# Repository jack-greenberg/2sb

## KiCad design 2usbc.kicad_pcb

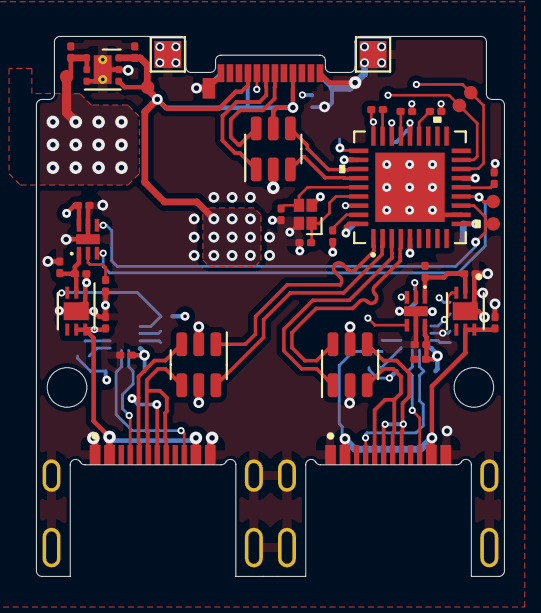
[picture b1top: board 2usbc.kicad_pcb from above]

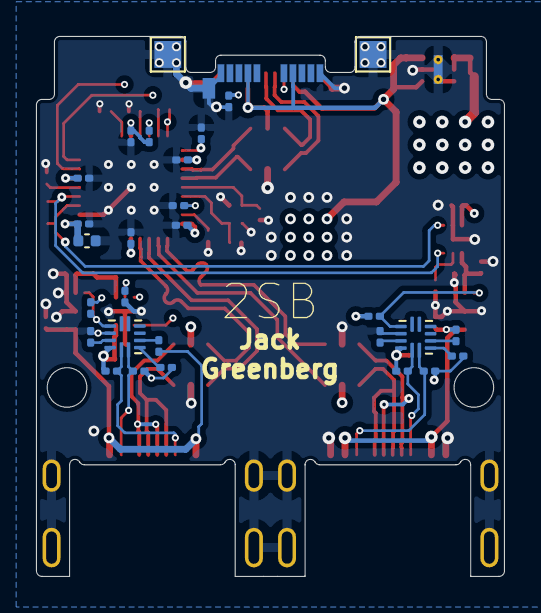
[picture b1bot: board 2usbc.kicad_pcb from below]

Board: 4 copper layers, 26.0 x 30.0 mm, 71 parts (28 on the bottom side), 48 nets.

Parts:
C101, C304, C404: 1uF; C_0201_0603Metric
C102: 2.2uF; C_0201_0603Metric
C201, C203, C205, C206, C207, C208: 10nF; C_0201_0603Metric
C202, C204: 6pF; C_0201_0603Metric
C209, C211, C301, C302, C305, C401, C402, C405: 0.1uF; C_0201_0603Metric
C210: 2uF; C_0402_1005Metric
C303, C403: 10uF; C_0201_0603Metric
H101, H102: MountingHole; MountingHole_2.2mm_M2
J101: USB_C_Plug_USB2.0; USB_C_Plug_Molex_105444
J102, J103: USB_C_Receptacle_USB2.0; USB4520
R101: 5.1K; R_0201_0603Metric
R201, R204, R205, R206, R207, R305, R405: 100K; R_0201_0603Metric
R208: 12K; R_0201_0603Metric
R301, R401: 330R; R_0201_0603Metric
R302, R303, R402, R403: 56K; R_0201_0603Metric
R304, R404: 900K; R_0201_0603Metric
R306, R406: 10K; R_0201_0603Metric
R307, R407: 10k; R_0201_0603Metric
TP101, TP102, TP103, TP104: TestPoint; TestPoint_Pad_1.5x1.5mm
TP105, TP106, TP301, TP302, TP401, TP402: TestPoint; TestPoint_MD
U101: TLV76733DRVx; WSON-6-1EP_2x2mm_P0.65mm_EP1x1.6mm_ThermalVias
U102, U301, U401: USBLC6-2SC6; SOT-23-6
U201: USB2512B; USB2512-AEZG
U302, U402: TMLF-6_MT_MCH; MIC2097-1YMT-TR
U303, U403: TUSB320; Texas_X2QFN-12_1.6x1.6mm_P0.4mm
U304, U404: AP2161W; SON50P181X201X60-7N
Y201: 24MHz; XTAL_ABM12W-24.0000MHZ-6-D1X-T3

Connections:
+3V3: C102.1, C201.1, C203.1, C205.1, C206.1, C207.1, C208.1, C210.1, R201.1, R207.1, TP106.1, U101.1 (OUT), U101.2 (SNS), U201.5 (VDDA33), U201.10 (VDDA33), U201.15 (VDD33), U201.23 (VDD33), U201.27 (VBUS_DET), U201.29 (VDDA33), U201.36 (VDDA33)
/HOST_CC: J101.A5 (CC), R101.1
/Hub IC/P1_ENABLE: TP301.1, U201.12 (PRTPWR1/BC_EN1), U302.4 (ENABLE)
/Hub IC/P1_OVER_CURRENT: TP302.1, U201.13 (OCS_N1), U302.3 (~FAULT)
/Hub IC/P2_ENABLE: TP401.1, U201.16 (PRTPWR2/BC_EN2), U402.4 (ENABLE)
/Hub IC/P2_OVER_CURRENT: TP402.1, U201.17 (OCS_N2), U402.3 (~FAULT)
/Hub IC/USB_P1_DN: U201.1 (USBDM_DN1/PRT_DIS_M1), U301.1 (I/O1)
/Hub IC/USB_P1_DP: U201.2 (USBDP_DN1/PRT_DIS_P1), U301.6 (I/O1)
/Hub IC/USB_P2_DN: U201.3 (USBDM_DN2/PRT_DIS_M2), U401.1 (I/O1)
/Hub IC/USB_P2_DP: U201.4 (USBDP_DN2/PRT_DIS_P2), U401.6 (I/O1)
/Hub IC/~RESET: R201.2, U201.26 (RESET_N)
/Output Stage 1/ID: R306.2, U303.9 (ID), U304.3 (~EN)
/Output Stage 1/ILIMIT: R301.1, U302.2 (ILIMIT)
/Output Stage 1/OUT_USB_DN: J102.A7 (D-), J102.B7 (D-), U301.3 (I/O2)
/Output Stage 1/OUT_USB_DP: J102.A6 (D+), J102.B6 (D+), U301.4 (I/O2)
/Output Stage 1/PORT: R307.2, U303.3 (PORT)
/Output Stage 1/VBUS_DET: R304.1, U303.4 (VBUS_DET)
/Output Stage 1/VOUT_I_LIM: C302.2, C303.2, U302.1 (VOUT), U304.2 (IN)
/Output Stage 1/~EN: R305.1, U303.11 (~EN)
/Output Stage 2/ID: R406.2, U403.9 (ID), U404.3 (~EN)
/Output Stage 2/ILIMIT: R401.1, U402.2 (ILIMIT)
/Output Stage 2/OUT_USB_DN: J103.A7 (D-), J103.B7 (D-), U401.3 (I/O2)
/Output Stage 2/OUT_USB_DP: J103.A6 (D+), J103.B6 (D+), U401.4 (I/O2)
/Output Stage 2/PORT: R407.2, U403.3 (PORT)
/Output Stage 2/VBUS_DET: R404.1, U403.4 (VBUS_DET)
/Output Stage 2/VOUT_I_LIM: C402.2, C403.2, U402.1 (VOUT), U404.2 (IN)
/Output Stage 2/~EN: R405.1, U403.11 (~EN)
/P1_CC1: J102.A5 (CC1), R302.1, U303.1 (CC1)
/P1_CC2: J102.B5 (CC2), R303.1, U303.2 (CC2)
/P1_VBUS: C304.2, J102.A4 (VBUS), J102.B4 (VBUS), R304.2, U304.5 (OUT), U304.6 (OUT)
/P2_CC1: J103.A5 (CC1), R402.1, U403.1 (CC1)
/P2_CC2: J103.B5 (CC2), R403.1, U403.2 (CC2)
/P2_VBUS: C404.2, J103.A4 (VBUS), J103.B4 (VBUS), R404.2, U404.5 (OUT), U404.6 (OUT)
/USB_HOST_DN: J101.A7 (D-), U102.6 (I/O1)
/USB_HOST_DP: J101.A6 (D+), U102.1 (I/O1)
/USB_PROTECT_HOST_DN: U102.4 (I/O2), U201.30 (USBDM_UP)
/USB_PROTECT_HOST_DP: U102.3 (I/O2), U201.31 (USBDP_UP)
GND: C101.2, C102.2, C201.2, C202.2, C203.2, C204.2, C205.2, C206.2, C207.2, C208.2, C209.2, C210.2, C211.2, C301.1, C302.1, C303.1, C304.1, C305.1, C401.1, C402.1, C403.1, C404.1, C405.1, J101.A1 (GND), J101.A12 (GND), J101.B1 (GND), J101.B12 (GND), J101.S1 (SHIELD), J102.A1 (GND), J102.B1 (GND), J102.S1 (SHIELD), J103.A1 (GND), J103.B1 (GND), J103.S1 (SHIELD), R101.2, R204.2, R205.2, R206.2, R208.2, R301.2, R305.2, R401.2, R405.2, TP101.1, TP102.1, TP103.1, TP104.1, U101.3 (GND), U101.5 (GND), U101.7 (PAD), U102.2 (GND), U201.11 (TEST), U201.37 (EPAD), U301.2 (GND), U302.5 (GND), U302.7 (EPAD), U303.10 (GND), U304.1 (GND), U304.7 (PAD), U401.2 (GND), U402.5 (GND), U402.7 (EPAD), U403.10 (GND), U404.1 (GND), U404.7 (PAD), Y201.2, Y201.4
unnamed: C209.1, U201.14 (CRFILT)
unnamed: R207.2, U201.25 (HS_IND/CFG_SEL1)
unnamed: C211.1, U201.34 (PLLFILT)
unnamed: R208.1, U201.35 (RBIAS)
unnamed: R206.1, U201.24 (SCL/SMBCLK/CFG_SEL0)
unnamed: R204.1, U201.22 (SDA/SMBDATA/NON_REM1)
unnamed: R205.1, U201.28 (SUSP_IND/LOCAL_PWR/NON_REM0)
unnamed: C202.1, U201.33 (XTALIN/CLKIN), Y201.1
unnamed: C204.1, U201.32 (XTALOUT), Y201.3
VBUS: C101.1, C301.2, C305.2, C401.2, C405.2, J101.A4 (VBUS), J101.A9 (VBUS), J101.B4 (VBUS), J101.B9 (VBUS), R302.2, R303.2, R306.1, R307.1, R402.2, R403.2, R406.1, R407.1, TP105.1, U101.4 (EN), U101.6 (IN), U102.5 (VBUS), U301.5 (VBUS), U302.6 (VIN), U303.12 (VDD), U401.5 (VBUS), U402.6 (VIN), U403.12 (VDD)

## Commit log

2023-03-03 Update CC resistors with feedback
2023-03-10 Add power switch ic and channel config ic
2023-03-13 Layout checkpoint
2023-03-13 Update layout to be a bit more symmetrical
2023-04-24 Update schematic with feedback
2023-05-30 Add schematic PDF

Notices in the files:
2usbc.kicad_pcb:
This work is licensed under a Creative Commons Attribution 4.0 International License
